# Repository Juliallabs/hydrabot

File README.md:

# Hydrabot

### Uma maquina IOT revolucionaria que permite que você receba um copo de água de qualquer lugar do mundo
*A revolucionary IOT machine that allows you to recieve a glass of water from any part of the world*

BOM LIST
|COMPONENTE|QUANTIDADE|POSIÇÃO|PART NUMBER|
|---|---|---|---|
|   |   |   |   |
|   |   |   |   |
|   |   |   |   |

REFERENCIA PARA COMPRAS
|COMPONENTE|QUANTIDADE|REFERÊNCIA|
|---|---|---|
|PEMN1   |   |[metaltex](https://www.eletrodex.com.br/pemn1-conector-placa-cabo-passo-2-50mm-macho-90-metaltex.html)  |
|FEF1   |   |[meltaltex](https://www.eletrodex.com.br/pef1-conector-metaltex-passo-2-50mm-alojamento.html)   |
|Terminal Macho PET1|   | [mateltex](https://www.eletrodex.com.br/terminal-macho-pet1-para-conector-pe-2-50mm.html) |

COMO FUNCIONA?

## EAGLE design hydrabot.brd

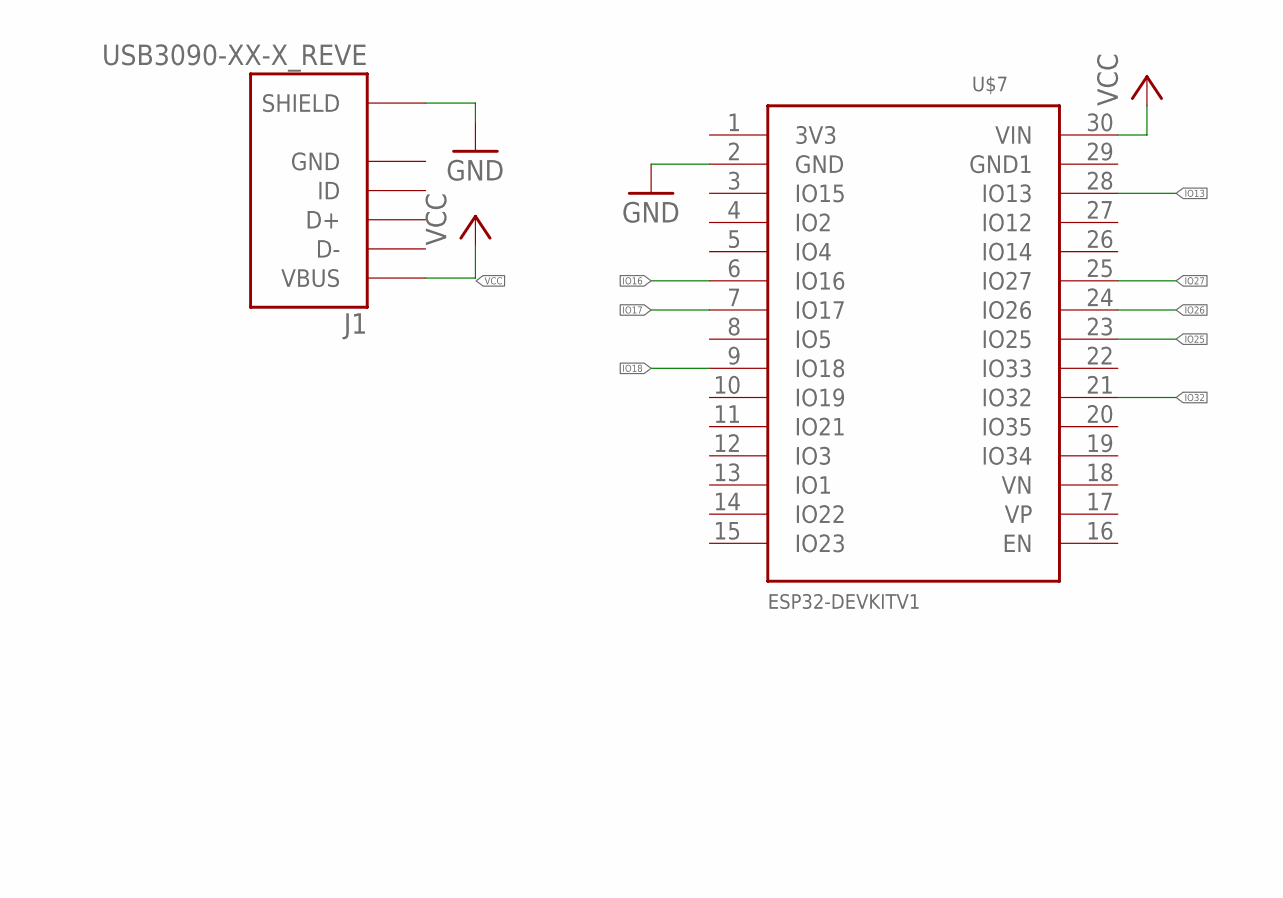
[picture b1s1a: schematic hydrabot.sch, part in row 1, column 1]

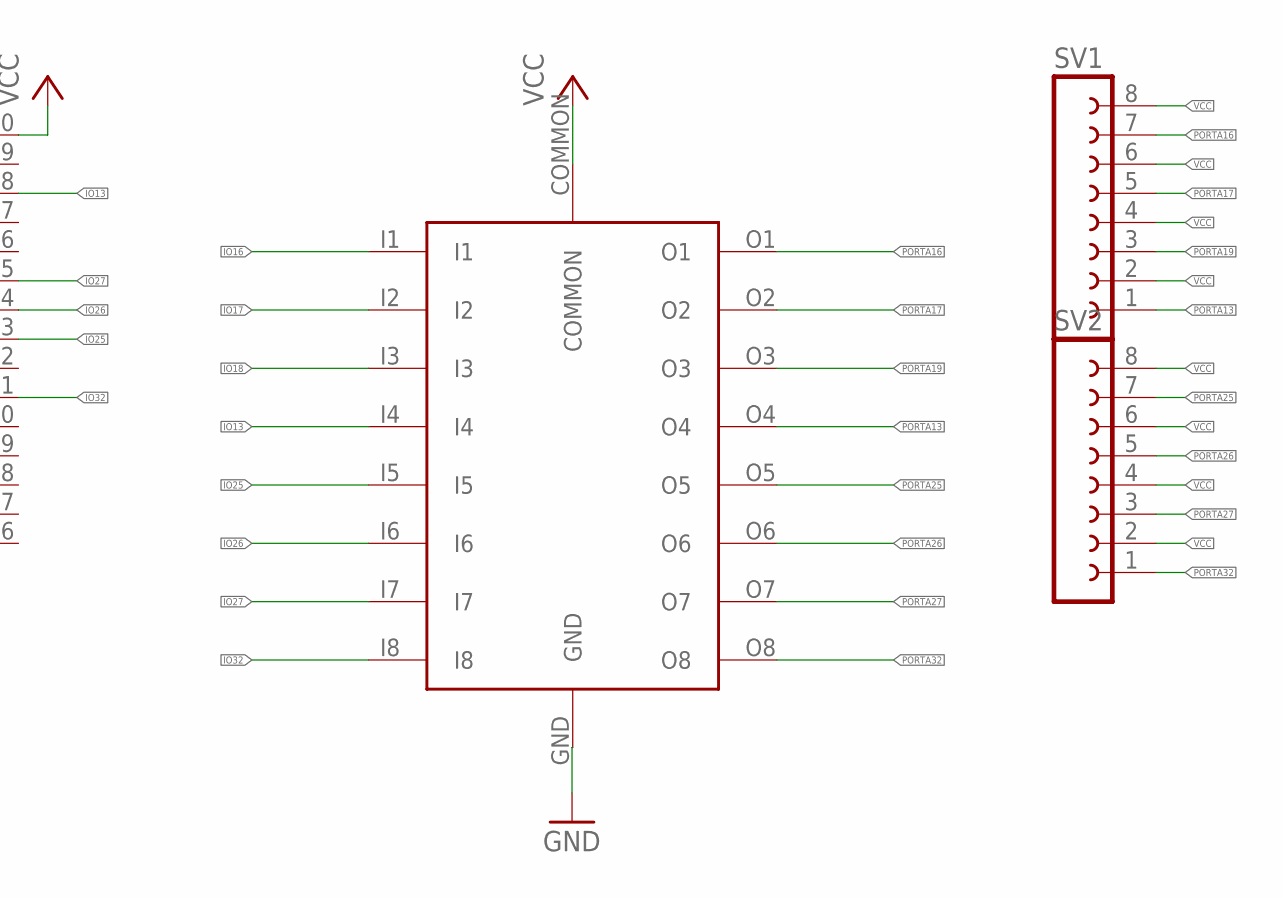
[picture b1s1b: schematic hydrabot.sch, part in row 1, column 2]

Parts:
J1: USB3090-XX-X_REVE; GCT_USB3090-XX-X_REVE
SV1, SV2: FE08-1; FE08
U$7: ESP32DEVKITV1; ESP32-DEVKITV1
ULN2803: ULN2803AFW

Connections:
GND: J1.5 (GND), J1.6 (SHIELD), J1.7 (SHIELD), J1.8 (SHIELD), J1.9 (SHIELD), U$7.2 (GND), ULN2803.GND
IO13: U$7.28 (IO13), ULN2803.I4
IO16: U$7.6 (IO16), ULN2803.I1
IO17: U$7.7 (IO17), ULN2803.I2
IO18: U$7.9 (IO18), ULN2803.I3
IO25: U$7.23 (IO25), ULN2803.I5
IO26: U$7.24 (IO26), ULN2803.I6
IO27: U$7.25 (IO27), ULN2803.I7
IO32: U$7.21 (IO32), ULN2803.I8
PORTA13: SV1.1, ULN2803.O4
PORTA16: SV1.7, ULN2803.O1
PORTA17: SV1.5, ULN2803.O2
PORTA19: SV1.3, ULN2803.O3
PORTA25: SV2.7, ULN2803.O5
PORTA26: SV2.5, ULN2803.O6
PORTA27: SV2.3, ULN2803.O7
PORTA32: SV2.1, ULN2803.O8
VCC: J1.1 (VBUS), SV1.2, SV1.4, SV1.6, SV1.8, SV2.2, SV2.4, SV2.6, SV2.8, U$7.30 (VIN), ULN2803.COMMON

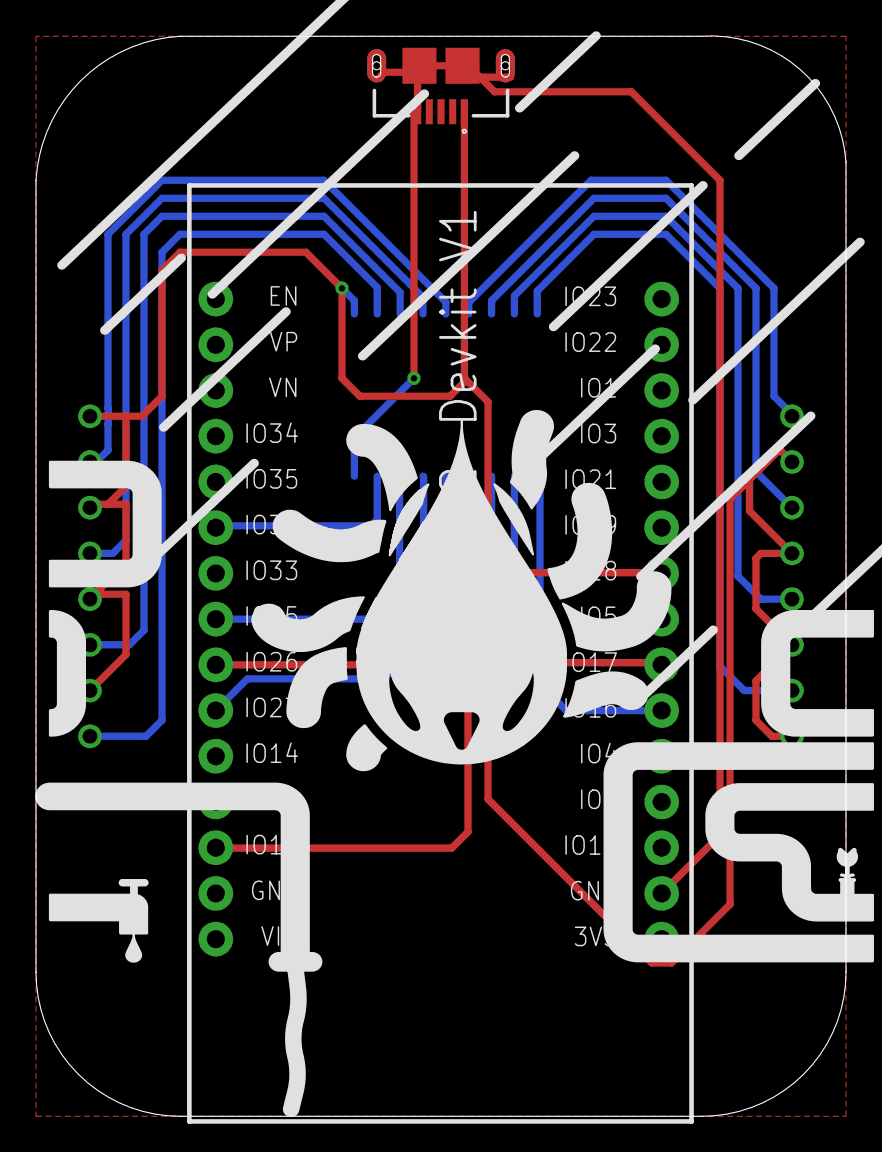
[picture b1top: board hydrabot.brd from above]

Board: 2 copper layers, 45.0 x 60.0 mm, 5 parts (1 on the bottom side), 18 nets.

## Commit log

2021-01-07 init project
2021-01-07 Rename options.json to options-exemplo.json
2021-01-08 att arquivos
2021-03-22 atualização de arquivos
2021-05-06 add main
2021-05-09 refatoração de nomes de variaveis
2021-05-09 Adiciona imagem do hydrabot no readme
2021-05-09 Criação das pastas de imagens e de pcb
